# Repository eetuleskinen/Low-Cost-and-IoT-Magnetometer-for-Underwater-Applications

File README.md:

# Low Cost and IoT Magnetometer for Underwater Applications

Finish LPF product for AD823A is in the AD823AN folder. I didn't change the file name because I don't want to risk anything. Later I will try to change it. (.zip folder)

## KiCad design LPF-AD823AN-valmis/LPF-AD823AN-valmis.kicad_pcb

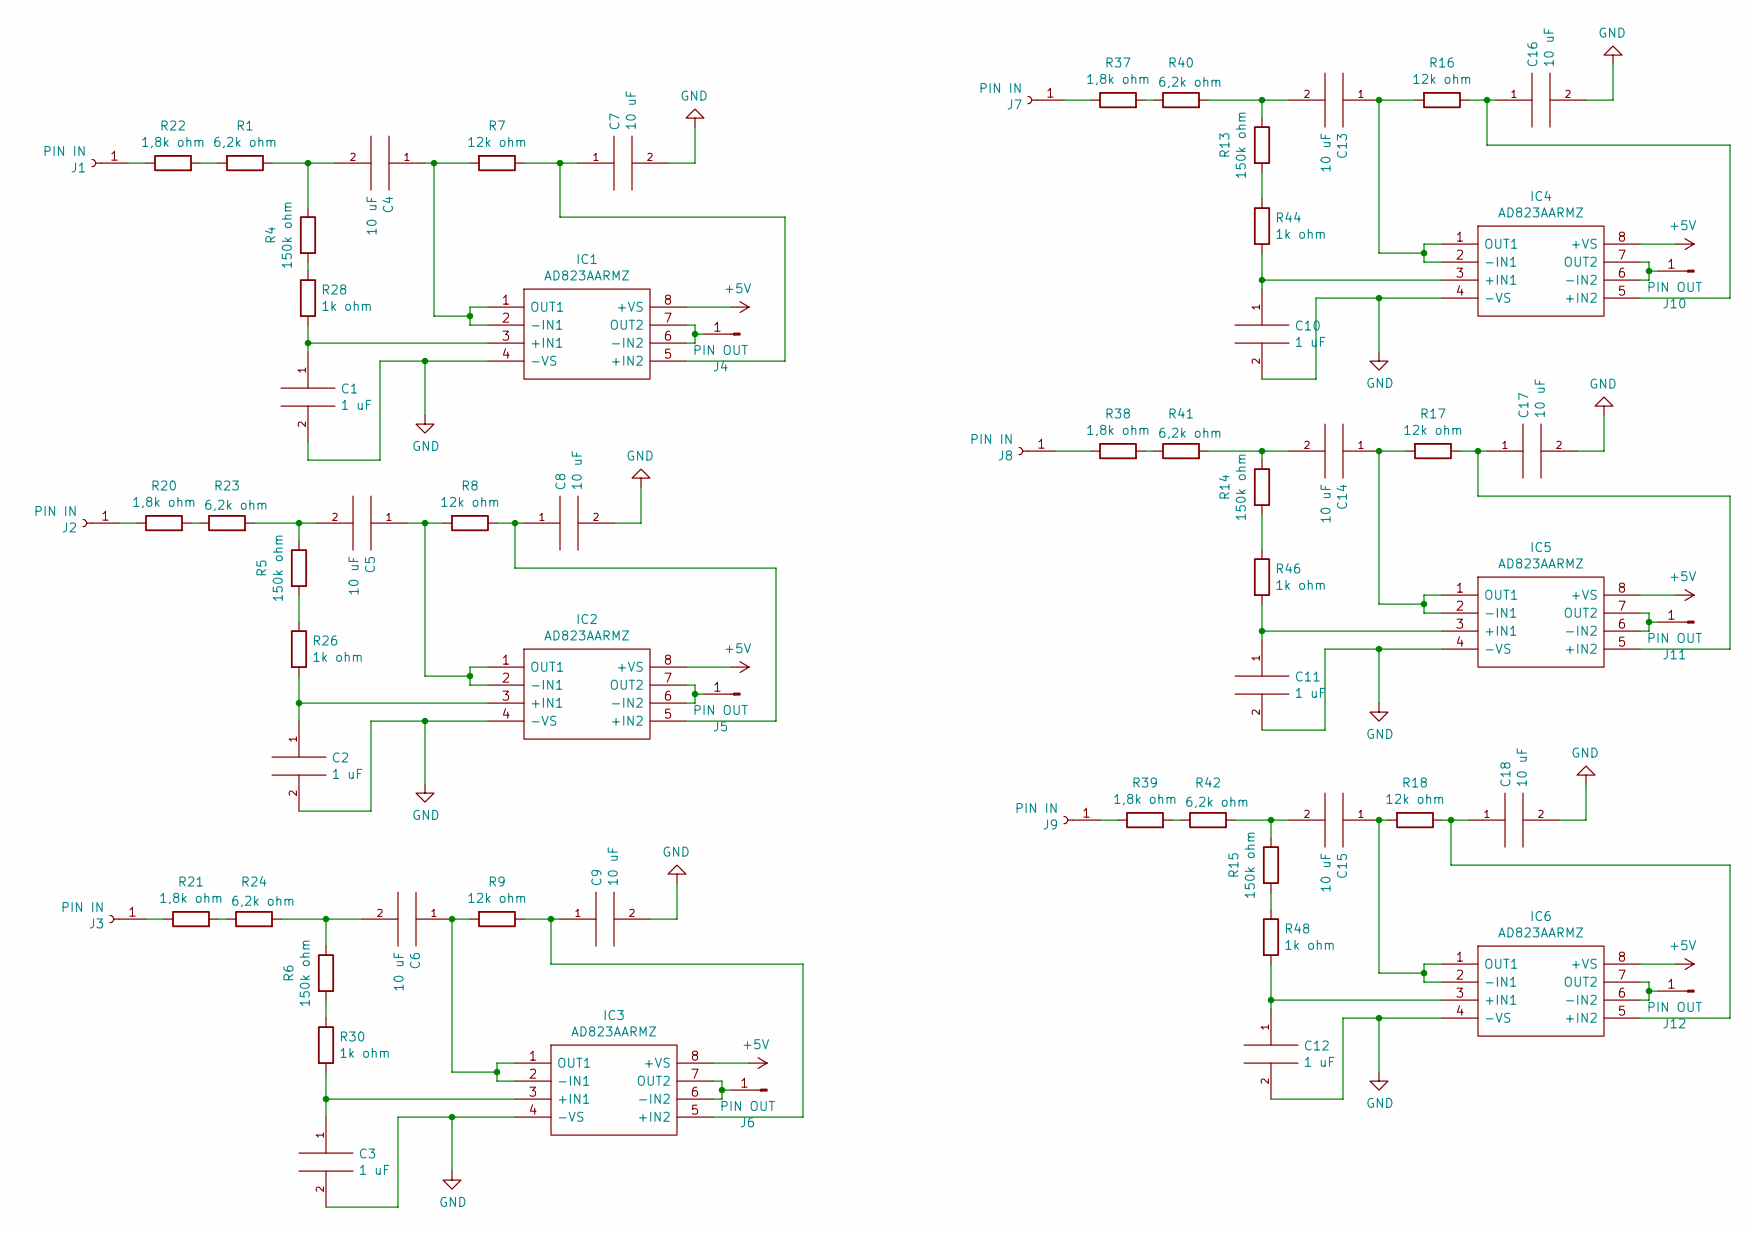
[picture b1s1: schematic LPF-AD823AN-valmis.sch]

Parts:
C1, C2, C3, C10, C11, C12: 1 uF; ECWFD2W105JB
C4: 10 uF; CUSTOM_MKP1839610164
C5, C6, C7, C8, C9, C13, C14, C15, C16, C17, C18: 10 uF; MKP1848S61070JP2C
IC1, IC2, IC3, IC4, IC5, IC6: AD823AARMZ; SOP65P490X110-8N; Manufacturer_Part_Number AD823AARMZ; Mouser Part Number 584-AD823AARMZ
J1, J2, J3, J7, J8, J9: PIN IN; PinHeader_1x01_P1.00mm_Vertical
J4, J5, J6, J10, J11, J12: PIN OUT; PinHeader_1x01_P1.00mm_Vertical
R1, R23, R24, R40, R41, R42: 6,2k ohm; RESC6432X120N
R4, R5, R6, R13, R14, R15: 150k ohm; RESC6432X120N
R7, R8, R9, R16, R17, R18: 12k ohm; RESC6432X120N
R20, R21, R22, R37, R38, R39: 1,8k ohm; RESC6432X120N
R26, R28, R30, R44, R46, R48: 1k ohm; RESC6432X120N

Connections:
+5V: IC1.8 (+VS), IC2.8 (+VS), IC3.8 (+VS), IC4.8 (+VS), IC5.8 (+VS), IC6.8 (+VS)
GND: C1.2, C2.2, C3.2, C7.2, C8.2, C9.2, C10.2, C11.2, C12.2, C16.2, C17.2, C18.2, IC1.4 (-VS), IC2.4 (-VS), IC3.4 (-VS), IC4.4 (-VS), IC5.4 (-VS), IC6.4 (-VS)
unnamed: C1.1, IC1.3 (+IN1), R28.2
unnamed: C2.1, IC2.3 (+IN1), R26.2
unnamed: C3.1, IC3.3 (+IN1), R30.2
unnamed: C4.1, IC1.1 (OUT1), IC1.2 (-IN1), R7.2
unnamed: C4.2, R1.1, R4.1
unnamed: C5.1, IC2.1 (OUT1), IC2.2 (-IN1), R8.2
unnamed: C5.2, R5.1, R23.2
unnamed: C6.1, IC3.1 (OUT1), IC3.2 (-IN1), R9.2
unnamed: C6.2, R6.1, R24.2
unnamed: C7.1, IC1.5 (+IN2), R7.1
unnamed: C8.1, IC2.5 (+IN2), R8.1
unnamed: C9.1, IC3.5 (+IN2), R9.1
unnamed: C10.1, IC4.3 (+IN1), R44.2
unnamed: C11.1, IC5.3 (+IN1), R46.2
unnamed: C12.1, IC6.3 (+IN1), R48.2
unnamed: C13.1, IC4.1 (OUT1), IC4.2 (-IN1), R16.2
unnamed: C13.2, R13.1, R40.2
unnamed: C14.1, IC5.1 (OUT1), IC5.2 (-IN1), R17.2
unnamed: C14.2, R14.1, R41.2
unnamed: C15.1, IC6.1 (OUT1), IC6.2 (-IN1), R18.2
unnamed: C15.2, R15.1, R42.2
unnamed: C16.1, IC4.5 (+IN2), R16.1
unnamed: C17.1, IC5.5 (+IN2), R17.1
unnamed: C18.1, IC6.5 (+IN2), R18.1
unnamed: IC1.6 (-IN2), IC1.7 (OUT2), J4.1
unnamed: IC2.6 (-IN2), IC2.7 (OUT2), J5.1
unnamed: IC3.6 (-IN2), IC3.7 (OUT2), J6.1
unnamed: IC4.6 (-IN2), IC4.7 (OUT2), J10.1
unnamed: IC5.6 (-IN2), IC5.7 (OUT2), J11.1
unnamed: IC6.6 (-IN2), IC6.7 (OUT2), J12.1
unnamed: J1.1, R22.1
unnamed: J2.1, R20.1
unnamed: J3.1, R21.1
unnamed: J7.1, R37.1
unnamed: J8.1, R38.1
unnamed: J9.1, R39.1
unnamed: R1.2, R22.2
unnamed: R13.2, R44.1
unnamed: R14.2, R46.1
unnamed: R15.2, R48.1
unnamed: R20.2, R23.1
unnamed: R21.2, R24.1
unnamed: R5.2, R26.1
unnamed: R4.2, R28.1
unnamed: R6.2, R30.1
unnamed: R37.2, R40.1
unnamed: R38.2, R41.1
unnamed: R39.2, R42.1

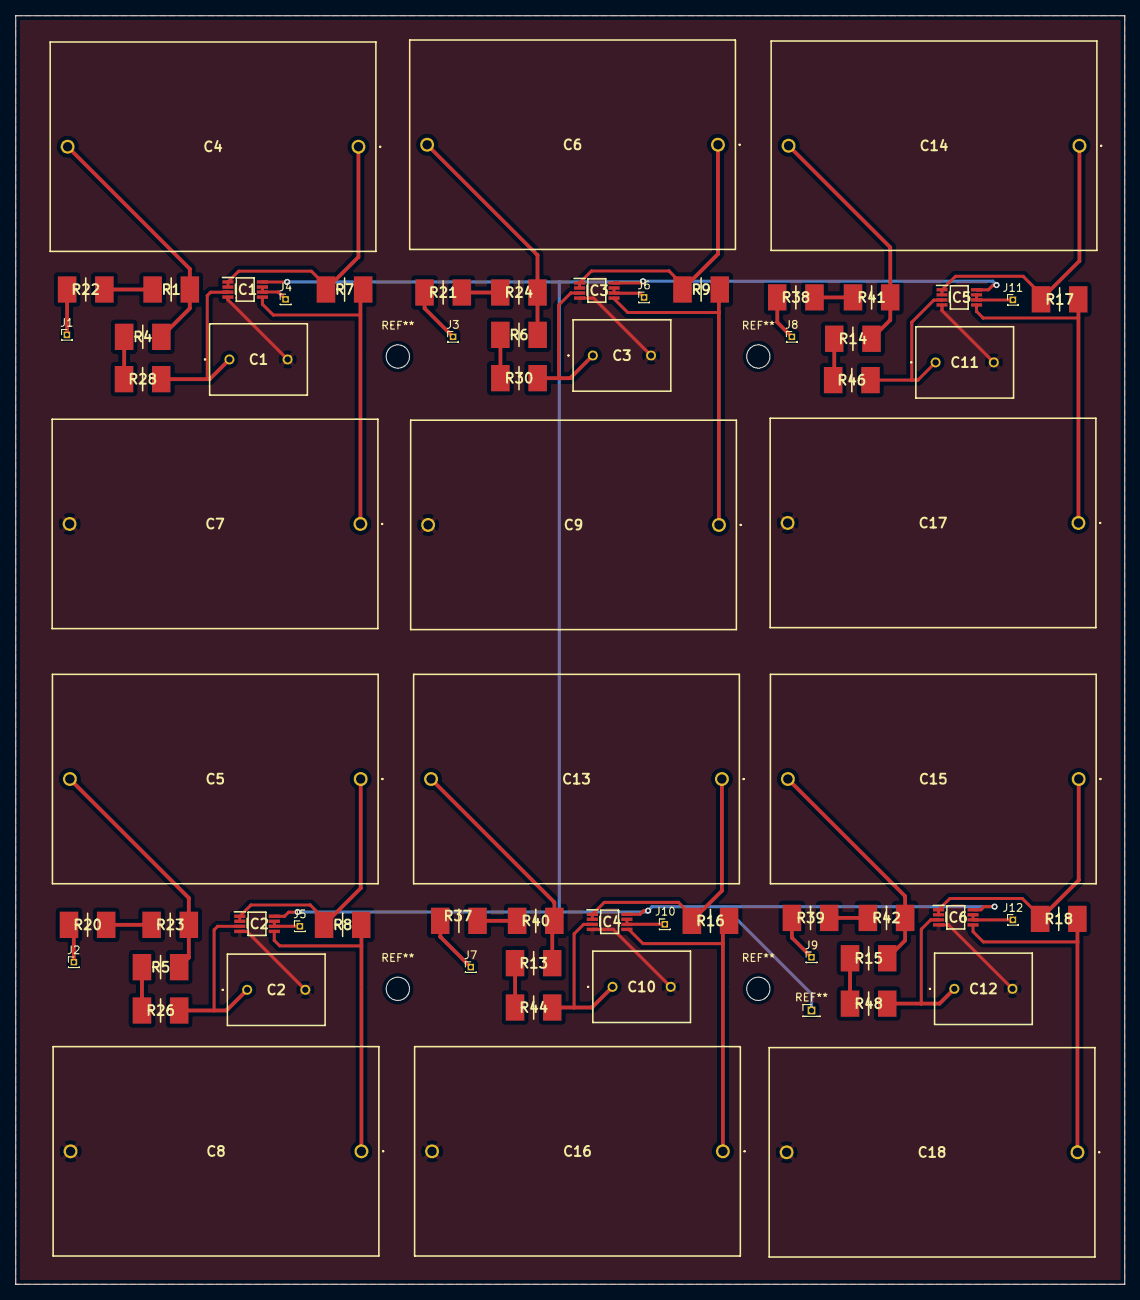
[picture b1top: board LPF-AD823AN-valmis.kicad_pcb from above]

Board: 2 copper layers, 143.0 x 163.6 mm, 66 parts (0 on the bottom side), 50 nets.
